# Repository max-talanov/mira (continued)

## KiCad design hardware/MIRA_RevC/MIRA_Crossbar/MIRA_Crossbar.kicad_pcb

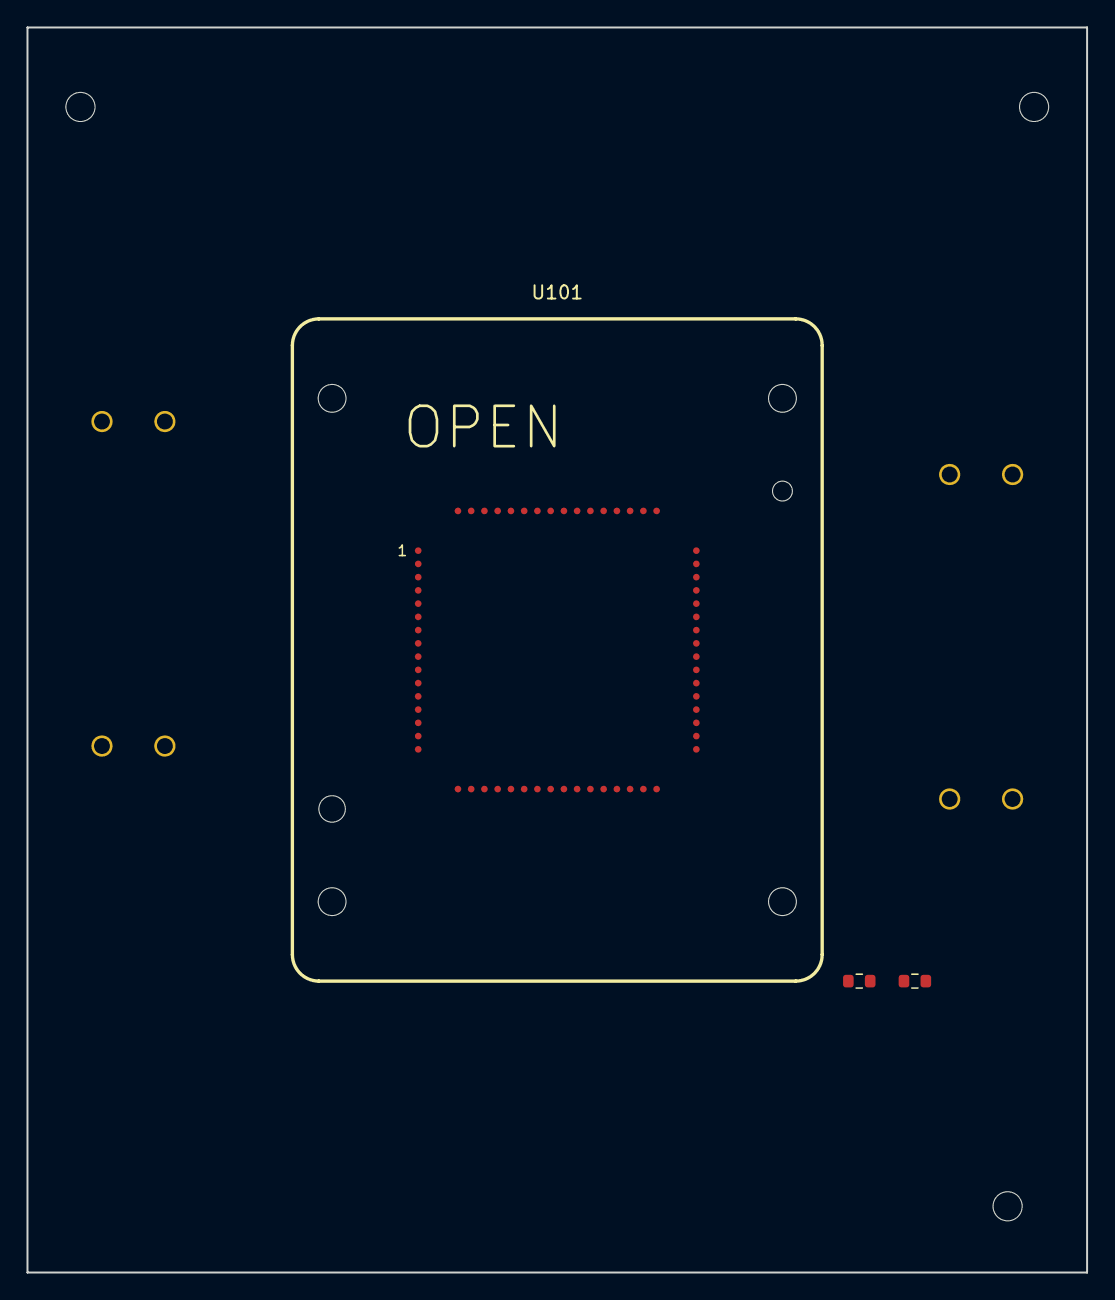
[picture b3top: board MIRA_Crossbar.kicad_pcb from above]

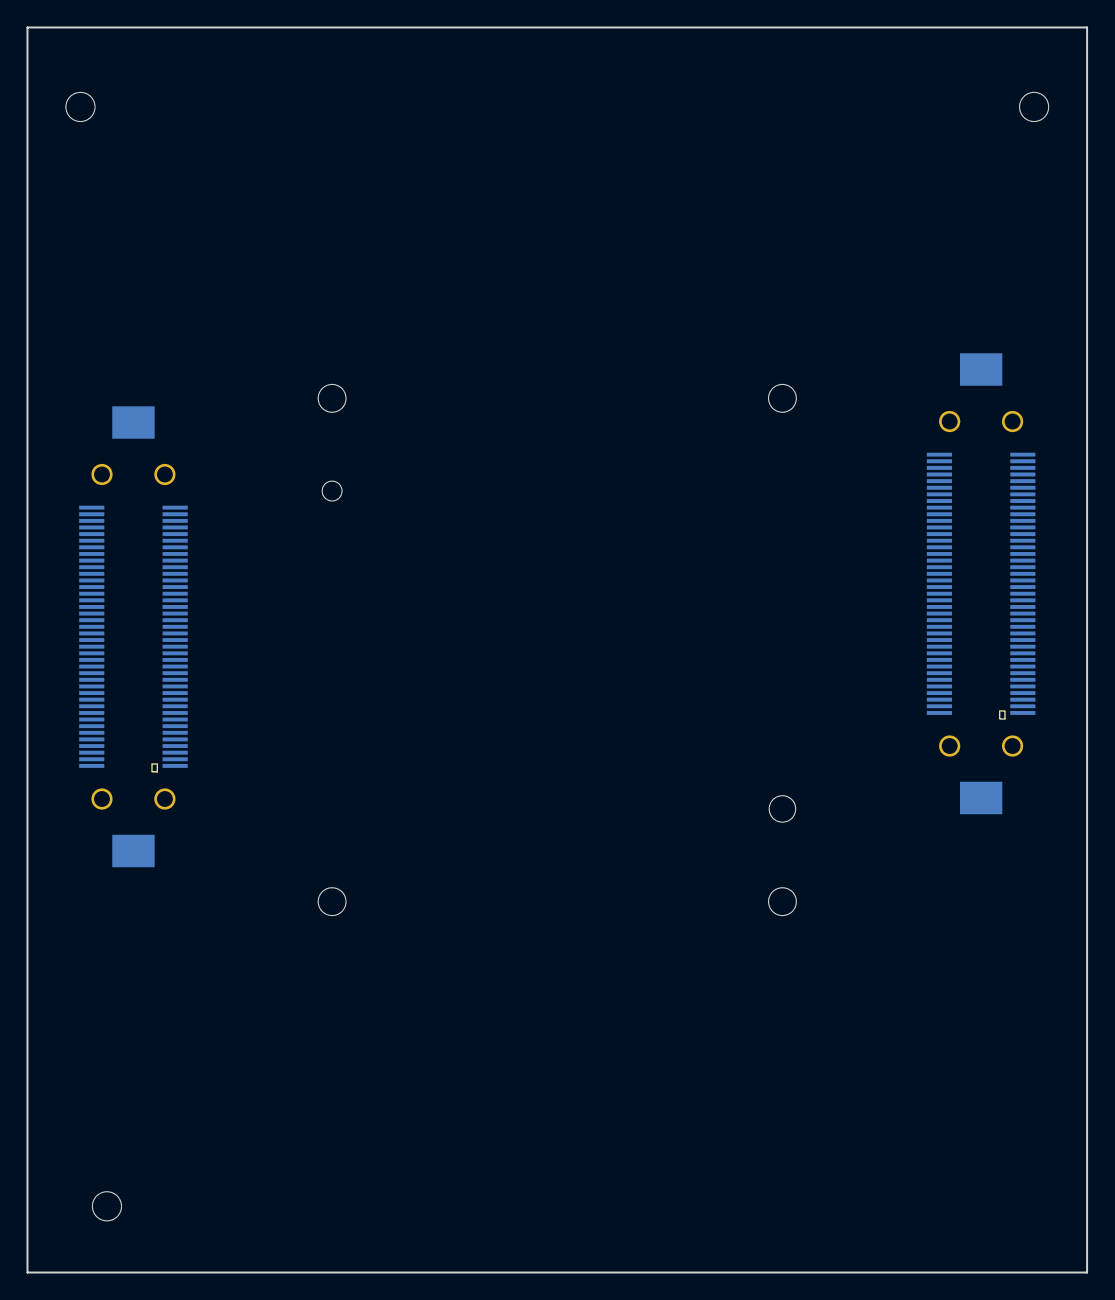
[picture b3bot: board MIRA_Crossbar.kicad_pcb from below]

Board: 2 copper layers, 80.0 x 94.0 mm, 8 parts (2 on the bottom side), 51 nets, no tracks yet.

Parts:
H1, H2: M2 spacer8mm / D2.2
H3: KEY receive D2.2
J101, J102: FX23L-80P-0.5SV8; Hirose_FX23L-80P-0.5SV8
R101, R102: 0R fitted; R_0603_1608Metric
U101: ICS-CQFP64-1830-1830-100-1

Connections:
CASE: R101.1, U101.40 (CONTACT)
CH0: J101.1, U101.64 (CONTACT)
CH1: J101.2, U101.63 (CONTACT)
CH2: J101.4, U101.62 (CONTACT)
CH3: J101.5, U101.61 (CONTACT)
CH4: J101.7, U101.60 (CONTACT)
CH5: J101.8, U101.59 (CONTACT)
CH6: J101.10, U101.58 (CONTACT)
CH7: J101.11, U101.57 (CONTACT)
CH8: J101.13, U101.56 (CONTACT)
CH9: J101.14, U101.55 (CONTACT)
CH10: J101.16, U101.54 (CONTACT)
CH11: J101.17, U101.53 (CONTACT)
CH12: J101.19, U101.52 (CONTACT)
CH13: J101.20, U101.51 (CONTACT)
CH14: J101.22, U101.50 (CONTACT)
CH15: J101.23, U101.49 (CONTACT)
CH16: J101.25, U101.17 (CONTACT)
CH17: J101.26, U101.18 (CONTACT)
CH18: J101.28, U101.19 (CONTACT)
CH19: J101.29, U101.20 (CONTACT)
CH20: J101.31, U101.21 (CONTACT)
CH21: J101.32, U101.22 (CONTACT)
CH22: J101.34, U101.23 (CONTACT)
CH23: J101.35, U101.24 (CONTACT)
CH24: J101.37, U101.25 (CONTACT)
CH25: J101.38, U101.26 (CONTACT)
CH26: J101.40, U101.27 (CONTACT)
CH27: J101.41, U101.28 (CONTACT)
CH28: J101.43, U101.29 (CONTACT)
CH29: J101.44, U101.30 (CONTACT)
CH30: J101.46, U101.31 (CONTACT)
CH31: J101.47, U101.32 (CONTACT)
CH32: J102.1, U101.3 (CONTACT)
CH33: J102.2, U101.4 (CONTACT)
CH34: J102.4, U101.5 (CONTACT)
CH35: J102.5, U101.6 (CONTACT)
CH36: J102.7, U101.7 (CONTACT)
CH37: J102.8, U101.8 (CONTACT)
CH38: J102.10, U101.9 (CONTACT)
CH39: J102.11, U101.10 (CONTACT)
CH40: J102.13, U101.46 (CONTACT)
CH41: J102.14, U101.45 (CONTACT)
CH42: J102.16, U101.44 (CONTACT)
CH43: J102.17, U101.43 (CONTACT)
CH44: J102.19, U101.42 (CONTACT)
CH45: J102.20, U101.41 (CONTACT)
CH46: J102.22, U101.39 (CONTACT)
CH47: J102.23, U101.38 (CONTACT)
GND: J101.3, J101.6, J101.9, J101.12, J101.15, J101.18, J101.21, J101.24, J101.27, J101.30, J101.33, J101.36, J101.39, J101.42, J101.45, J101.48, J101.51, J101.54, J101.57, J101.60, J101.63, J101.66, J101.P1, J101.P2, J101.P3, J101.P4, J102.3, J102.6, J102.9, J102.12, J102.15, J102.18, J102.21, J102.24, J102.27, J102.30, J102.33, J102.36, J102.39, J102.42, J102.45, J102.48, J102.51, J102.54, J102.57, J102.60, J102.63, J102.66, J102.P1, J102.P2, J102.P3, J102.P4, R101.2, R102.2
GND_REF: R102.1, U101.48 (CONTACT)

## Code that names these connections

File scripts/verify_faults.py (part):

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  p,c=maps['Power'],maps['Control']
  def pins(board,ref,expect):
   ck(board+'_'+ref+'_pins',all(maps[board].get((ref,str(pin)))==net for pin,net in expect.items()))
  pins('Power','U2501',{1:'AON',5:'AON',6:'PM_WDI',7:'PM_WDO_N',8:'AON_RESET_N',2:'unconnected-(U2501-CWD-Pad2)'})
  pins('Power','U2502',{1:'SYS3V3',5:'SYS3V3',6:'HOST_WDI',7:'HOST_WDO_N',8:'HOST_RESET_N',2:'unconnected-(U2502-CWD-Pad2)'})
  pins('Power','U2603',{2:'AON',4:'AON',12:'AON',10:'AON',3:'PWR_ARM_PULSE',11:'MATRIX_ARM_PULSE',5:'GLOBAL_PWR_PERMIT',9:'MATRIX_PERMIT_RAW'})
  pins('Power','D2501',{1:'AON_RESET_N',2:'PM_WDO_N',3:'PM_RESET_N'})
  pins('Power','U2401',{11:'HOST_ALIVE_PM',12:'PM_RESET_N',15:'PM_WDI',16:'PM_WDO_N',49:'HOST_WDO_N',4:'GLOBAL_CLEAR_N',5:'LINK_READY_H'})
  pins('Power','U3301',{5:'MATRIX_PERMIT',6:'MATRIX_PERMIT_POWER',4:'GND',14:'SYS3V3'})
  pins('Power','J4901',{1:'HOST_WDI',3:'HOST_ALIVE',13:'MATRIX_PERMIT_POWER',15:'HOST_RESET_N',17:'MATRIX_INHIBIT_N'})
  pins('Control','J400',{1:'HOST_WDI',3:'HOST_ALIVE',13:'MATRIX_PERMIT_POWER',15:'HOST_RESET_N',17:'MATRIX_INHIBIT_N'})
  pins('Control','U100',{166:'HOST_WDI',56:'HOST_ALIVE',33:'HOST_RESET_N'})
  pins('Control','R402',{1:'MATRIX_PERMIT_POWER',2:'GND'})
  pins('Control','U401',{2:'MATRIX_PERMIT_POWER',4:'MATRIX_PERMIT',5:'IO3V3'})
  pins('Power','R2509',{1:'HOST_RESET_N',2:'SYS3V3'})
  pins('Power','R2508',{1:'HOST_WDO_N',2:'AON'})
  pins('Control','U1301',{6:'MAT_ALLOWED',1:'MAT_CONFIG_LATCH',2:'MAT_ARM_DATA',5:'MAT_IMAGE_ARMED',7:'IO3V3'})
  pins('Control','U1336',{1:'MAT_FRAME_VALID',2:'MAT_REQUEST_VALID_RAW',4:'MAT_ARM_DATA'})
  pins('Control','U1331',{1:'MAT_SPI_LATCH',2:'MAT_SPI_OE_N',4:'MAT_CONFIG_LATCH'})
  pins('Control','U1305',{2:'MAT_RUN',4:'MAT_OE_N'})
  for ref in ['U1404','U1405','U1406','U1407','U1408','U1409']:pins('Control',ref,{13:'MAT_OE_N',10:'MAT_ALLOWED'})
  for ref in ['Q2101','Q2104','Q2106']:pins('Power',ref,{1:'MATRIX_PERMIT',2:'GND'})
  pins('Power','U5405',{2:'HOST_WDO_N',4:'HOST_RESET_N',5:'AON',3:'GND'})
  ck('PM_watchdog_parts_exact',all(comps['Power'][r].findtext('value')=='TPS3851H33EDRBR' for r in ['U2501','U2502']))
  # Compile the actual AND/inverter topology. Other signals are explicitly supplied states.
  graphs={}
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   ck(signal+'_PM_KILL_path_disables_matrix',not killed['matrix_permit'] and killed['MAT_OE_N'])
   results.append({'event':signal+' lost while heartbeat continues','hardware_detection':'message/progress validity requires firmware to stop application heartbeat or assert KILL','at_fault':f,'after_PM_asserts_MATRIX_KILL':killed})
  # MCU kill signals drive grounded-source MOSFETs at the actual clear input nets.
  pins('Power','Q2601',{1:'PWR_KILL_GPIO',2:'GND',3:stop})
  pins('Power','Q2602',{1:'MATRIX_KILL_GPIO',2:'GND',3:'MATRIX_INHIBIT_N'})
  model=Machine();model.step({'HOST_WDO_N':False},marm=True);held=model.step(marm=True)
  ck('ARM_held_high_through_fault_does_not_rearm',not held['matrix_permit'])
  model.step();ck('fresh_ARM_edge_after_fault_is_required',model.step(marm=True)['matrix_permit'])
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
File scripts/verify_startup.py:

#!/usr/bin/env python3
"""Native KiCad startup repair checks; fixed pin contract plus before/after audit."""
from pathlib import Path
import json,subprocess,tempfile,xml.etree.ElementTree as ET,itertools,hashlib
from verify_unpowered_signals import SIGNAL_REFS
from verify_fault_hardware import FAULT_REFS,normalize_fault_rows
ROOT=Path(__file__).resolve().parents[1]
OUT=ROOT/'docs/pcb-preparation/startup/validation'
CHANNELS=['USB','SYS','FPGA','ANA','P15','N15','CORE','AUX18','AUX25','IO33','DDR','PHY','VTT','ANA5','ANA33','MATRIX']
NEW_REFS={'R1805'}|{f'U{x}' for x in range(5201,5204)}|{f'R{x}' for x in range(5201,5205)}|{f'C{x}' for x in range(5201,5204)}|{f'U{x}' for x in range(5301,5309)}|{f'C{x}' for x in range(5301,5309)}|{f'R{x}' for x in range(5301,5317)}
LEGACY_CLEAR='/POWER_SYSTEM/POWER_CONTROL/2600_PM_PERMIT_INTERLOCKS/GLOBAL_CLEAR_N'

def normalize_startup_rows(rows):
 """Undo ONLY the explicit repair for the older connector regression baseline."""
 out=[]
 for ref,pin,net in normalize_fault_rows(rows):
  if ref in NEW_REFS:continue
  # Sequencing feedback added on 2026-10-29: only this exact pin/net maps back.
  if (ref,pin,net)==('U2401','4','GLOBAL_CLEAR_N'):net='unconnected-(U2401-PC14-Pad4)'
  if net.startswith('CMD_') and net.endswith('_RAW') and ref.startswith(('U27','U28','R27','R28')):net=net[:-4]
  if (ref,pin)==('U2603','9') and net=='MATRIX_PERMIT_RAW':net='MATRIX_PERMIT'
  if (ref,pin) in [('U2601','8'),('U2603','1')] and net in ['GLOBAL_CLEAR_RAW_N','GLOBAL_CLEAR_N']:net=LEGACY_CLEAR
  out.append((ref,pin,net))
 out.extend([('Q1801','1','CMD_VTT'),('Q1801','2','EN_VTT'),('Q1801','3','AON')])
 return sorted(out)

def native(path):
 t=ET.parse(path);m={(n.get('ref'),n.get('pin')):net.get('name') for net in t.findall('nets/net') for n in net.findall('node')}
 c={n.get('ref'):n for n in t.findall('components/comp')};return t,m,c

def main():
 OUT.mkdir(parents=True,exist_ok=True);checks={}
 def ck(n,v):
  checks[n]=bool(v)
  if not v:raise AssertionError(n)
 with tempfile.TemporaryDirectory() as td:
  fn=Path(td)/'Power.xml';subprocess.run(['kicad-cli','sch','export','netlist','--format','kicadxml','-o',str(fn),str(ROOT/'hardware/MIRA_Power/MIRA_Power.kicad_sch')],check=True)
  t,m,c=native(fn)
  def pins(ref,d):ck(ref+'_pin_contract',all(m.get((ref,str(k)))==v for k,v in d.items()))
  pins('U5201',{1:'STARTUP_RESET_N',2:'GND',3:'AON',4:'STARTUP_CT',5:'STARTUP_SENSE',6:'AON'})
  pins('U5202',{2:'STARTUP_RESET_N',3:'GND',4:'STARTUP_READY_H',5:'AON'})
  pins('U5203',{1:'GLOBAL_CLEAR_RAW_N',2:'STARTUP_READY_H',3:'GND',4:'GLOBAL_CLEAR_N',5:'AON'})
  for r,d in {'R5201':{1:'AON',2:'STARTUP_SENSE'},'R5202':{1:'STARTUP_SENSE',2:'GND'},'R5203':{1:'AON',2:'STARTUP_RESET_N'},'R5204':{1:'AON',2:'STARTUP_CT'}}.items():pins(r,d)
  for i in range(8):
   nets=['MATRIX_PERMIT' if a=='MATRIX' else 'CMD_'+a for a in CHANNELS[2*i:2*i+2]]
   pins(f'U{5301+i}',{1:'STARTUP_READY_H',2:nets[0]+'_RAW',6:nets[0],7:'STARTUP_READY_H',5:nets[1]+'_RAW',3:nets[1],8:'AON',4:'GND'})
   for j,net in enumerate(nets):pins(f'R{5301+2*i+j}',{1:net,2:'GND'})
  for ref in [f'C{x}' for x in range(5201,5204)]+[f'C{x}' for x in range(5301,5309)]:pins(ref,{1:'AON',2:'GND'})
  pins('U2401',{4:'GLOBAL_CLEAR_N'})
  pins('R1805',{1:'CMD_VTT',2:'EN_VTT'});pins('U1801',{7:'EN_VTT',10:'AON'});pins('U2603',{1:'GLOBAL_CLEAR_N',9:'MATRIX_PERMIT_RAW'});pins('U2601',{8:'GLOBAL_CLEAR_RAW_N'})
  ck('old_VTT_source_follower_removed','Q1801' not in c)
  ck('matrix_connector_uses_qualified_permit',m['J2603','1']=='MATRIX_PERMIT')
  ck('ready_fanout_is_16_OE_clear_and_monitor_buffer',{k for k,v in m.items() if v=='STARTUP_READY_H'}=={('U5202','4'),('U5203','2'),('U6100','2')}|{(f'U{r}',pin) for r in range(5301,5309) for pin in ['1','7']})
  expected_values={'R1805':'0R','R5201':'590k','R5202':'100k','R5203':'150k','R5204':'100k','U5201':'TPS3808G01DBVR','U5202':'74AUP1G34GW','U5203':'74LVC1G08GV'}
  for i,ch in enumerate(CHANNELS):expected_values[f'R{5301+i}']='10k' if ch in ['VTT','MATRIX'] else ('47k' if ch=='N15' else '220k')
  for r in range(5301,5309):expected_values[f'U{r}']='74AUP2G126DC'
  for r,v in expected_values.items():ck(r+'_value',c[r].findtext('value')==v)
  before=json.loads((OUT/'baseline-power-pins.json').read_text())['pins'];after=[[*k,v] for k,v in sorted(m.items())]
  ck('all_unrelated_legacy_pins_preserved',normalize_startup_rows(after)==[tuple(x) for x in before])
  ck('new_component_set_exact',{r for r in c if r not in {x[0] for x in before}}==NEW_REFS|FAULT_REFS|SIGNAL_REFS)
  # All actual signal consumers retain their former nets; only the listed drivers move to RAW.
  changes=[{'ref':r,'pin':pin,'before':old,'after':m.get((r,pin))} for r,pin,old in before if m.get((r,pin))!=old]
  (OUT/'pin-delta.json').write_text(json.dumps(changes,indent=2)+'\n')
  # Match new symbol pin numbers to the local footprint pad numbers.
  for ref in sorted(NEW_REFS):
   comp=c[ref];fp=comp.findtext('footprint');file=ROOT/'hardware/MIRA_Power/libraries/MIRA_RevA.pretty'/(fp.split(':')[1]+'.kicad_mod')
   import re
   pads=set(re.findall(r'\(pad\s+"?(\d+)"?\s',file.read_text()))
   pins_used={pin for r,pin in m if r==ref}
   ck(ref+'_footprint_pin_set',pins_used==pads)
  erc=OUT/'Power-erc.json';subprocess.run(['kicad-cli','sch','erc','--format','json','--severity-all','--exit-code-violations','-o',str(erc),str(ROOT/'hardware/MIRA_Power/MIRA_Power.kicad_sch')],check=True)
  erc_data=json.loads(erc.read_text());ck('61_active_Power_sheets',len(erc_data['sheets'])==61);ck('zero_erc_messages',not any(s['violations'] for s in erc_data['sheets']))
 # Abstract sequential contract, explicitly not transistor or transient simulation.
 seq=[];q=0;prev_clk=0
 for event,ready,clear,clk in [('cold start',0,0,0),('ARM while blocked',0,1,1),('release ARM',0,1,0),('AON ready',1,1,0),('ARM',1,1,1),('release ARM',1,1,0),('AON fault',0,1,0),('AON restored',1,1,0),('fresh ARM',1,1,1)]:
  clr=ready and clear
  if not clr:q=0
  elif clk and not prev_clk:q=1
  prev_clk=clk;seq.append({'event':event,'ready':ready,'clear':clr,'arm':clk,'permit':q,'output_enable':bool(ready and q)})
 ck('no_automatic_rearm',seq[7]['permit']==0 and seq[8]['permit']==1)
 # DC corner arithmetic from cited datasheets, -40..85 C.
 thresholds=[.405*(1+sv*.02)*(1+590000*(1+st*.01)/(100000*(1+sb*.01)))+si*25e-9*590000*(1+st*.01) for sv,st,sb,si in itertools.product([-1,1],repeat=4)]
 margins={'supervisor_reset_pullup_plus_input_uA_below_1_3V':1.3/(150000*.99)*1e6+.5,'supervisor_POR_load_limit_uA':15,'AUP_ready_fanout_uA':16*.5+5+5,'AUP_light_load_limit_uA':20,'POR_VOL_max_V':.2,'AUP_VIL_at_0_8V_V':.8*.3,'buffer_ready_VOL_max_V':.1,'VTT_VOH_conservative_min_at_3V_V':2.55,'TPS51200_EN_VIH_V':1.7,'VTT_logic_high_margin_V':.85,'sense_falling_nominal_V':.405*6.9,'sense_falling_corner_min_V':min(thresholds),'sense_falling_corner_max_V':max(thresholds),'sense_rising_upper_with_3pct_hysteresis_V':max(thresholds)+.405*.03*6.9,'added_output_pulldown_current_nominal_mA':(13*3.28/220000+3.28/47000+2*3.28/10000)*1000,'added_bypass_uF':1.1,'recommended_extra_AON_budget_mA':5,'scope':'DC design arithmetic only; no measured ramps, fast-collapse immunity, temperature test or SPICE result.'}
 ck('POR_load_margin',margins['supervisor_reset_pullup_plus_input_uA_below_1_3V']<15);ck('ready_fanout_margin',margins['AUP_ready_fanout_uA']<20);ck('POR_logic_low_margin',.2<.8*.3);ck('VTT_high_margin',2.55>1.7)
 result={'kicad_version':subprocess.check_output(['kicad-cli','version'],text=True).strip(),'checks_passed':len(checks),'checks':checks,'changed_legacy_pin_entries':len(changes),'removed_pins':3,'new_pin_entries':len(m)-len(before)+3,'startup_components':len(NEW_REFS),'fault_components':len(FAULT_REFS),'new_components':len(NEW_REFS|FAULT_REFS|SIGNAL_REFS),'matrix_and_rail_channels':16,'sequence_model':seq,'dc_margins':margins,'hardware_tests':'pending'}
 (OUT/'summary.json').write_text(json.dumps(result,indent=2)+'\n');print(json.dumps({k:v for k,v in result.items() if k not in ['checks','sequence_model','dc_margins']},indent=2))
if __name__=='__main__':main()

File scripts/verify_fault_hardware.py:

#!/usr/bin/env python3
"""Fault repair: strict native pin delta, package checks and ideal timed contract.

Not SPICE, MCU firmware, metastability or a measured board timing result.
"""
import hashlib,json,re,subprocess,tempfile
from pathlib import Path
from verify_unpowered_signals import SIGNAL_REFS,normalize_signal_rows
ROOT=Path(__file__).resolve().parents[1]
OUT=ROOT/'docs/pcb-preparation/fault-review/validation'
FAULT_REFS={f'U{x}' for x in range(5401,5406)}|{f'R{x}' for x in range(5401,5405)}|{f'C{x}' for x in range(5401,5406)}
LEGACY_CHANGES={('U2401','5'):('unconnected-(U2401-PC15-Pad5)','LINK_READY_H'),('U2602','13'):('AON','LINK_READY_H')}

def normalize_fault_rows(rows):
 out=[]
 for ref,pin,net in normalize_signal_rows(rows):
  if ref in FAULT_REFS:continue
  pair=LEGACY_CHANGES.get((ref,pin))
  if pair and net==pair[1]:net=pair[0]
  out.append((ref,pin,net))
 return sorted(out)

class LinkModel:
 """Ideal TPS3851 timeout plus asynchronous clear and first-edge flip-flop.

 reset is the supervisor's INTERNAL voltage/manual-reset state, not a
 readback of an externally pulled output pin. A falling WDI during clear
 cannot set Q. Timing exactly at a boundary is intentionally not qualified.
 """
 def __init__(self,timeout=200,pulse=200):
  self.timeout=timeout;self.pulse=pulse;self.ready=False;self.reset=True
  self.due=None;self.release=None;self.wdo=True;self.level=False
 def reset_at(self,t,asserted):
  self.reset=asserted;self.ready=False;self.wdo=True;self.release=None
  self.due=None if asserted else t+self.timeout
 def advance(self,t):
  while not self.reset:
   event=self.release if not self.wdo else self.due
   if event is None or event>t:break
   if self.wdo:
    self.wdo=False;self.ready=False;self.due=None;self.release=event+self.pulse
   else:
    self.wdo=True;self.release=None;self.due=event+self.timeout
 def drive(self,t,level):
  self.advance(t);fall=self.level and not level;self.level=level
  if fall and not self.reset and self.wdo:
   self.ready=True;self.due=t+self.timeout
 def beat(self,t):
  self.drive(t-5,True);self.drive(t,False)

def main():
 from verify_startup import native
 checks={};timing=[]
 def ck(name,value):
  checks[name]=bool(value)
  if not value:raise AssertionError(name)
 with tempfile.TemporaryDirectory() as td:
  f=Path(td)/'Power.xml'
  subprocess.run(['kicad-cli','sch','export','netlist','--format','kicadxml','-o',str(f),str(ROOT/'hardware/MIRA_Power/MIRA_Power.kicad_sch')],check=True)
  t,m,c=native(f)
  def pins(ref,expect):ck(ref+'_native_pins',all(m.get((ref,str(p)))==net for p,net in expect.items()))
  pins('U5401',{1:'AON',2:'LINK_CWD',3:'AON',4:'GND',5:'AON',6:'HOST_ALIVE_PM',7:'LINK_WDO_N',8:'LINK_RESET_N',9:'GND'})
  pins('U5402',{1:'unconnected-(U5402-NC-Pad1)',2:'HOST_ALIVE_PM',3:'GND',4:'LINK_EDGE_H',5:'AON'})
  pins('U5403',{1:'LINK_EDGE_H',2:'AON',4:'GND',5:'LINK_READY_H',6:'LINK_CLEAR_N',7:'AON',8:'AON'})
  pins('U5404',{1:'LINK_RESET_N',2:'LINK_WDO_N',3:'GND',4:'LINK_CLEAR_N',5:'AON'})
  pins('U5405',{2:'HOST_WDO_N',3:'GND',4:'HOST_RESET_N',5:'AON'})
  for r,a,b in [('R5401','AON','LINK_CWD'),('R5402','AON','LINK_RESET_N'),('R5403','AON','LINK_WDO_N'),('R5404','LINK_READY_H','GND')]:pins(r,{1:a,2:b})
  for i in range(5401,5406):pins('C'+str(i),{1:'AON',2:'GND'})
  pins('U2401',{5:'LINK_READY_H',11:'HOST_ALIVE_PM'})
  pins('U2602',{13:'LINK_READY_H'})
  ck('link_ready_has_only_intended_consumers',{k for k,v in m.items() if v=='LINK_READY_H'}=={('U5403','5'),('R5404','1'),('U2401','5'),('U2602','13')})
  ck('CWD_has_only_10k_and_timer',{k for k,v in m.items() if v=='LINK_CWD'}=={('R5401','2'),('U5401','2')})
  parts={'U5401':'TPS3851H33EDRBR','U5402':'74LVC1G14GV','U5403':'SN74LVC1G74DCUR','U5404':'74LVC1G08GV','U5405':'SN74LVC1G07DBVR','R5401':'10k','R5402':'10k','R5403':'10k','R5404':'100k',**{f'C{x}':'100n' for x in range(5401,5406)}}
  for ref,value in parts.items():ck(ref+'_part',c[ref].findtext('value')==value)
  # Native libpart electrical pin type, not just net names, proves wired-OR output.
  source=c['U5405'].find('libsource')
  lp=next(p for p in t.findall('libparts/libpart') if p.get('lib')==source.get('lib') and p.get('part')==source.get('part'))
  ck('host_reset_driver_is_open_collector',next(p for p in lp.findall('pins/pin') if p.get('num')=='4').get('type') =='open_collector')
  ck('no_AON_pullup_added_on_host_reset',not any(ref.startswith('R54') for ref,pin in m if m[ref,pin]=='HOST_RESET_N'))
  for ref in sorted(FAULT_REFS):
   fp=c[ref].findtext('footprint').split(':')[1]
   file=ROOT/'hardware/MIRA_Power/libraries/MIRA_RevA.pretty'/(fp+'.kicad_mod')
   pads=set(re.findall(r'\(pad\s+"?(\d+)"?\s',file.read_text()))
   ck(ref+'_footprint_pin_set',pads=={pin for r,pin in m if r==ref})
   model=re.findall(r'\(model\s+"([^"]+)"',file.read_text())
   ck(ref+'_local_3D_model',bool(model) and all((ROOT/'hardware/MIRA_Power'/name.replace('${KIPRJMOD}/','')).is_file() for name in model))
  baseline=json.loads((OUT/'baseline-sequencing-power-pins.json').read_text())['pins']
  after=[[*k,v] for k,v in sorted(m.items())]
  ck('only_two_documented_legacy_pin_changes',normalize_fault_rows(after)==[tuple(a) for a in baseline])
  ck('exactly_14_added_components',set(c)-SIGNAL_REFS-{a[0] for a in baseline}==FAULT_REFS and len(FAULT_REFS)==14)
  historical_m={(r,p):n for r,p,n in normalize_signal_rows(after)}
  delta=[{'ref':ref,'pin':pin,'before':old,'after':historical_m.get((ref,pin))} for ref,pin,old in baseline if historical_m.get((ref,pin))!=old]
  ck('legacy_delta_is_exact',len(delta)==2 and all((a['before'],a['after'])==LEGACY_CHANGES[a['ref'],a['pin']] for a in delta))
 # Datasheet timeout corners; no tolerance claim about propagation/detection ramps.
 for timeout in [170,200,230]:
  for pulse in [170,230]:
   tag=f'{timeout}ms_timeout_{pulse}ms_pulse'
   q=LinkModel(timeout,pulse);q.reset_at(0,False);q.advance(2000)
   ck(tag+'_no_first_edge_stays_blocked',not q.ready)
   q=LinkModel(timeout,pulse);q.reset_at(0,False)
   for moment in range(10,2011,50):q.beat(moment)
   ck(tag+'_50ms_heartbeat_stays_ready',q.ready and q.wdo)
   last=2010;q.advance(last+timeout-1)
   ck(tag+'_not_early',q.ready)
   q.advance(last+timeout)
   ck(tag+'_timeout_clears_readiness',not q.ready and not q.wdo)
   q.advance(last+timeout+pulse+1)
   ck(tag+'_WDO_release_does_not_restore_ready',q.wdo and not q.ready)
   q.beat(last+timeout+pulse+10)
   ck(tag+'_fresh_heartbeat_can_restore_ready',q.ready)
   q.reset_at(last+timeout+pulse+11,True)
   ck(tag+'_supply_reset_clears_ready',not q.ready)
   timing.append({'timeout_ms':timeout,'WDO_low_ms':pulse,'all_checks_passed':True})
 for level in [False,True]:
  q=LinkModel();q.reset_at(0,False);q.beat(10);q.drive(15,level);q.advance(211)
  ck('stuck_'+str(int(level))+'_blocks',not q.ready)
 q=LinkModel();q.reset_at(0,False);q.beat(10);q.advance(210);q.beat(250)
 ck('edge_during_clear_cannot_arm',not q.ready)
 q.advance(411);ck('ignored_edge_not_replayed_after_clear',not q.ready)
 ck('firmware_max_gap_below_min_timeout',100<170)
 result={'kicad_version':subprocess.check_output(['kicad-cli','version'],text=True).strip(),'checks_passed':len(checks),'checks':checks,'added_components':len(FAULT_REFS),'legacy_pin_changes':delta,'native_power_pin_net_sha256':hashlib.sha256(json.dumps(after,separators=(',',':')).encode()).hexdigest(),'timing_corners':timing,'heartbeat_design_target_ms':50,'heartbeat_firmware_max_gap_ms':100,'hardware_timeout_range_ms':[170,230],'extra_AON_budget_mA':2,'added_bypass_uF':0.5,'scope':'Native connectivity, packages and ideal event/latch model at valid supplies; not electrical transient, MCU firmware or prototype verification. Measure ramp, propagation, disconnect-to-stop, reset and unpowered-input behavior on hardware.'}
 (OUT/'hardware-summary.json').write_text(json.dumps(result,indent=2)+'\n')
 print(json.dumps({k:v for k,v in result.items() if k not in ['checks','timing_corners']},indent=2))
if __name__=='__main__':main()

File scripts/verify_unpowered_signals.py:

#!/usr/bin/env python3
"""Native delta and Ioff receiver pin contract. This is not electrical qualification."""
import json,subprocess,tempfile,hashlib,re,xml.etree.ElementTree as ET
from pathlib import Path
ROOT=Path(__file__).resolve().parents[1]
OUT=ROOT/'docs/pcb-preparation/unpowered-signals'
from verify_signal_remediation import ADDED as REMEDIATION_REFS, normalize_remediation_rows
V5_SIGNAL_REFS={'U5501','U5502','R5501','R5502','R5503','C5501','C5502'}
SIGNAL_REFS=V5_SIGNAL_REFS | REMEDIATION_REFS['Power']
SIGNAL_CHANGES={('U2602','10'):('HOST_RESET_N','HOST_RESET_AON_N'),('R3305','2'):('PM_UART_RX','HOST_UART_TX_RAW'),('R3306','1'):('PM_UART_RX','HOST_UART_TX_RAW')}
def normalize_signal_rows(rows):
 """Reverse only the documented v5 delta; historical baselines stay immutable."""
 out=[]
 for r,p,n in normalize_remediation_rows(rows,'Power'):
  if r in SIGNAL_REFS:continue
  pair=SIGNAL_CHANGES.get((r,p))
  if pair and n==pair[1]:n=pair[0]
  out.append((r,p,n))
 return sorted(out)
def main():
 from verify_signal_remediation import main as verify_v6
 verify_v6()
 checks={};digests={}
 def ck(n,v):
  checks[n]=bool(v)
  if not v:raise AssertionError(n)
 with tempfile.TemporaryDirectory() as td:
  for board in ['Power','Control']:
   f=Path(td)/(board+'.xml');subprocess.run(['kicad-cli','sch','export','netlist','--format','kicadxml','-o',str(f),str(ROOT/'hardware'/('MIRA_'+board)/('MIRA_'+board+'.kicad_sch'))],check=True)
   t=ET.parse(f);m={(n.get('ref'),n.get('pin')):net.get('name') for net in t.findall('nets/net') for n in net.findall('node')};c={n.get('ref'):n for n in t.findall('components/comp')}
   m={(r,p):n for r,p,n in normalize_remediation_rows([(*k,v) for k,v in m.items()],board)};c={r:v for r,v in c.items() if r not in REMEDIATION_REFS[board]}
   rows=sorted([*k,v] for k,v in m.items());baseline=json.loads((OUT/('baseline-v4-'+board.lower()+'-pins.json')).read_text())['pins']
   digests[board]=hashlib.sha256(json.dumps(rows,separators=(',',':')).encode()).hexdigest()
   ck(board+'_unrelated_pins_unchanged',(normalize_signal_rows(rows) if board=='Power' else [tuple(r) for r in rows])==[tuple(r) for r in baseline])
   if board=='Control':continue
   ck('exactly_seven_new_parts',set(c)-{r[0] for r in baseline}==V5_SIGNAL_REFS)
   delta=[{'ref':r,'pin':p,'before':n,'after':m.get((r,p))} for r,p,n in baseline if m.get((r,p))!=n]
   ck('exactly_three_legacy_pin_changes',len(delta)==3 and all((d['before'],d['after'])==SIGNAL_CHANGES[(d['ref'],d['pin'])] for d in delta))
   def pins(r,e):ck(r+'_pins',all(m.get((r,str(p)))==n for p,n in e.items()))
   pins('U5501',{1:'unconnected-(U5501-NC-Pad1)',2:'HOST_RESET_N',3:'GND',4:'HOST_RESET_AON_N',5:'AON'})
   pins('U5502',{1:'unconnected-(U5502-NC-Pad1)',2:'HOST_UART_TX_RAW',3:'GND',4:'PM_UART_RX',5:'AON'})
   for r,net in [('R5501','HOST_RESET_N'),('R5502','HOST_RESET_AON_N'),('R5503','PM_UART_RX')]:pins(r,{1:net,2:'GND'});ck(r+'_100k',c[r].findtext('value')=='100k')
   for r in ['C5501','C5502']:pins(r,{1:'AON',2:'GND'});ck(r+'_100n',c[r].findtext('value')=='100n')
   for r in ['U5501','U5502']:
    ck(r+'_exact_Ioff_MPN',c[r].findtext('value')=='74LVC1G17GV,125')
    source=c[r].find('libsource');lp=next(p for p in t.findall('libparts/libpart') if p.get('lib')==source.get('lib') and p.get('part')==source.get('part'))
    ck(r+'_power_input_output_types',{p.get('num'):p.get('type') for p in lp.findall('pins/pin')}=={'1':'no_connect','2':'input','3':'power_in','4':'output','5':'power_in'})
   pins('U2602',{10:'HOST_RESET_AON_N'});pins('R3305',{1:'HOST_UART_TX',2:'HOST_UART_TX_RAW'});pins('R3306',{1:'HOST_UART_TX_RAW',2:'GND'})
   ck('reset_AON_fanout_exact',{k for k,v in m.items() if v=='HOST_RESET_AON_N'}=={('U5501','4'),('U2602','10'),('R5502','1')})
   ck('UART_raw_fanout_exact',{k for k,v in m.items() if v=='HOST_UART_TX_RAW'}=={('U5502','2'),('R3305','2'),('R3306','1')})
   ck('UART_PM_fanout_exact',{k for k,v in m.items() if v=='PM_UART_RX'}=={('U5502','4'),('U2401','41'),('R5503','1')})
   for r in sorted(V5_SIGNAL_REFS):
    fp=c[r].findtext('footprint').split(':')[1];file=ROOT/'hardware/MIRA_Power/libraries/MIRA_RevA.pretty'/(fp+'.kicad_mod')
    ck(r+'_package_pin_numbers',set(re.findall(r'\(pad\s+"?(\d+)"?\s',file.read_text()))=={p for rr,p in m if rr==r})
   # Existing unresolved routes are made explicit, not silently called safe.
   pins('D3301',{2:'AON',3:'ADC_VTT'});pins('D3501',{2:'AON',3:'MON_V_INPUT'})
   pins('U3902',{24:'AON'})
 result={'date':'2026-10-30','checks_passed':len(checks),'checks':checks,'native_pin_sha256':digests,'added_components':7,'legacy_pin_changes':delta,'checklist_status':'Historical v5 regression; current status is in signal-remediation/README.md','scope':'Historical v5 connectivity regression after explicit v6 normalization; current actual-net validation runs first. No board measurement.','AON_budget_delta_mA':2,'AON_bypass_delta_uF':0.2}
 (OUT/'validation.json').write_text(json.dumps(result,ensure_ascii=False,indent=2)+'\n');print(json.dumps({k:v for k,v in result.items() if k!='checks'},ensure_ascii=False,indent=2))
if __name__=='__main__':main()
